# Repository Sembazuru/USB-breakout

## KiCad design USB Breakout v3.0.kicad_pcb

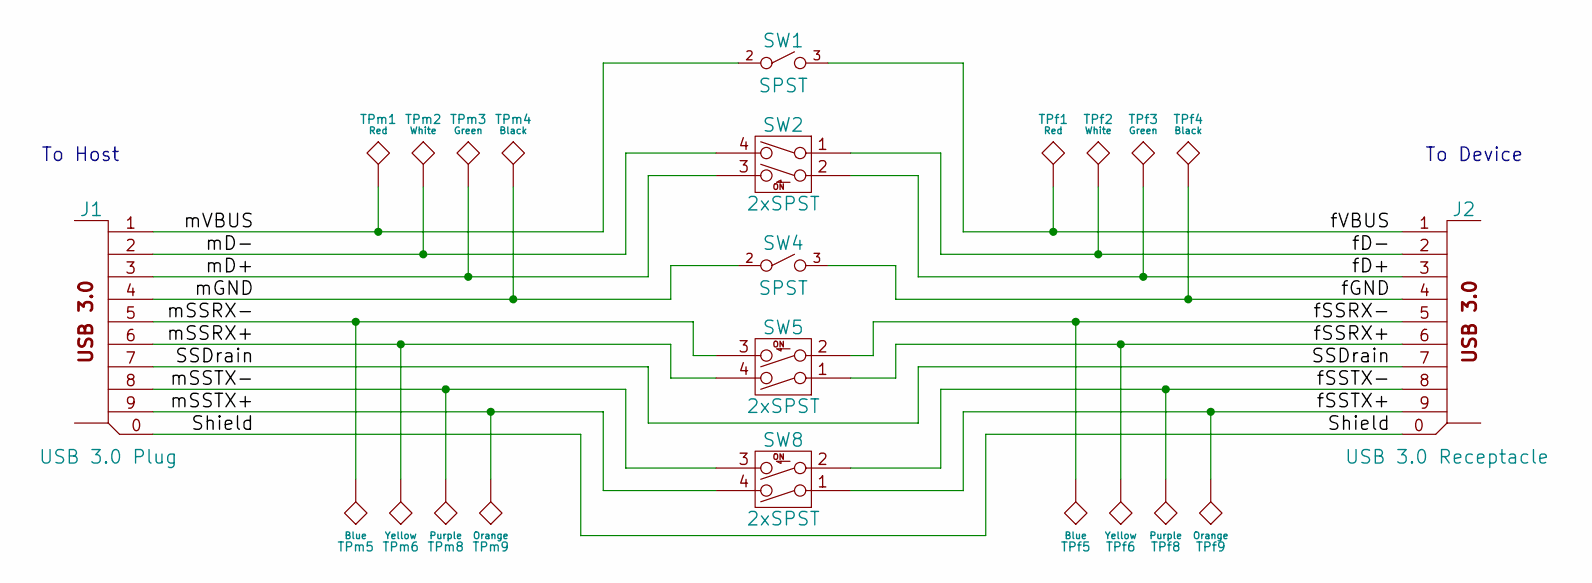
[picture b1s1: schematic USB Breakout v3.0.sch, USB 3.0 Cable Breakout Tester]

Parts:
J1: USB 3.0 Plug; Amphenol_GSB316441CEU
J2: USB 3.0 Receptacle; Amphenol_GSB311131HR
SW1, SW4: SPST; SW_Jameco2135478U
SW2, SW5, SW8: 2xSPST; DIPSW762W57P254L608H570Q4U
TPf1: Red; TESTPOINT
TPf2: White; TESTPOINT
TPf3: Green; TESTPOINT
TPf4: Black; TESTPOINT
TPf5: Blue; TESTPOINT
TPf6: Yellow; TESTPOINT
TPf8: Purple; TESTPOINT
TPf9: Orange; TESTPOINT
TPm1: Red; TESTPOINT
TPm2: White; TESTPOINT
TPm3: Green; TESTPOINT
TPm4: Black; TESTPOINT
TPm5: Blue; TESTPOINT
TPm6: Yellow; TESTPOINT
TPm8: Purple; TESTPOINT
TPm9: Orange; TESTPOINT

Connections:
/SSDrain: J1.7, J2.7
/Shield: J1.0, J2.0
/fD+: J2.3, SW2.2, TPf3.1
/fD-: J2.2, SW2.1, TPf2.1
/fGND: J2.4, SW4.3, TPf4.1
/fSSRX+: J2.6, SW5.1, TPf6.1
/fSSRX-: J2.5, SW5.2, TPf5.1
/fSSTX+: J2.9, SW8.1, TPf9.1
/fSSTX-: J2.8, SW8.2, TPf8.1
/fVBUS: J2.1, SW1.3, TPf1.1
/mD+: J1.3, SW2.3, TPm3.1
/mD-: J1.2, SW2.4, TPm2.1
/mGND: J1.4, SW4.2, TPm4.1
/mSSRX+: J1.6, SW5.4, TPm6.1
/mSSRX-: J1.5, SW5.3, TPm5.1
/mSSTX+: J1.9, SW8.4, TPm9.1
/mSSTX-: J1.8, SW8.3, TPm8.1
/mVBUS: J1.1, SW1.2, TPm1.1

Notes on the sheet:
To Host
To Device

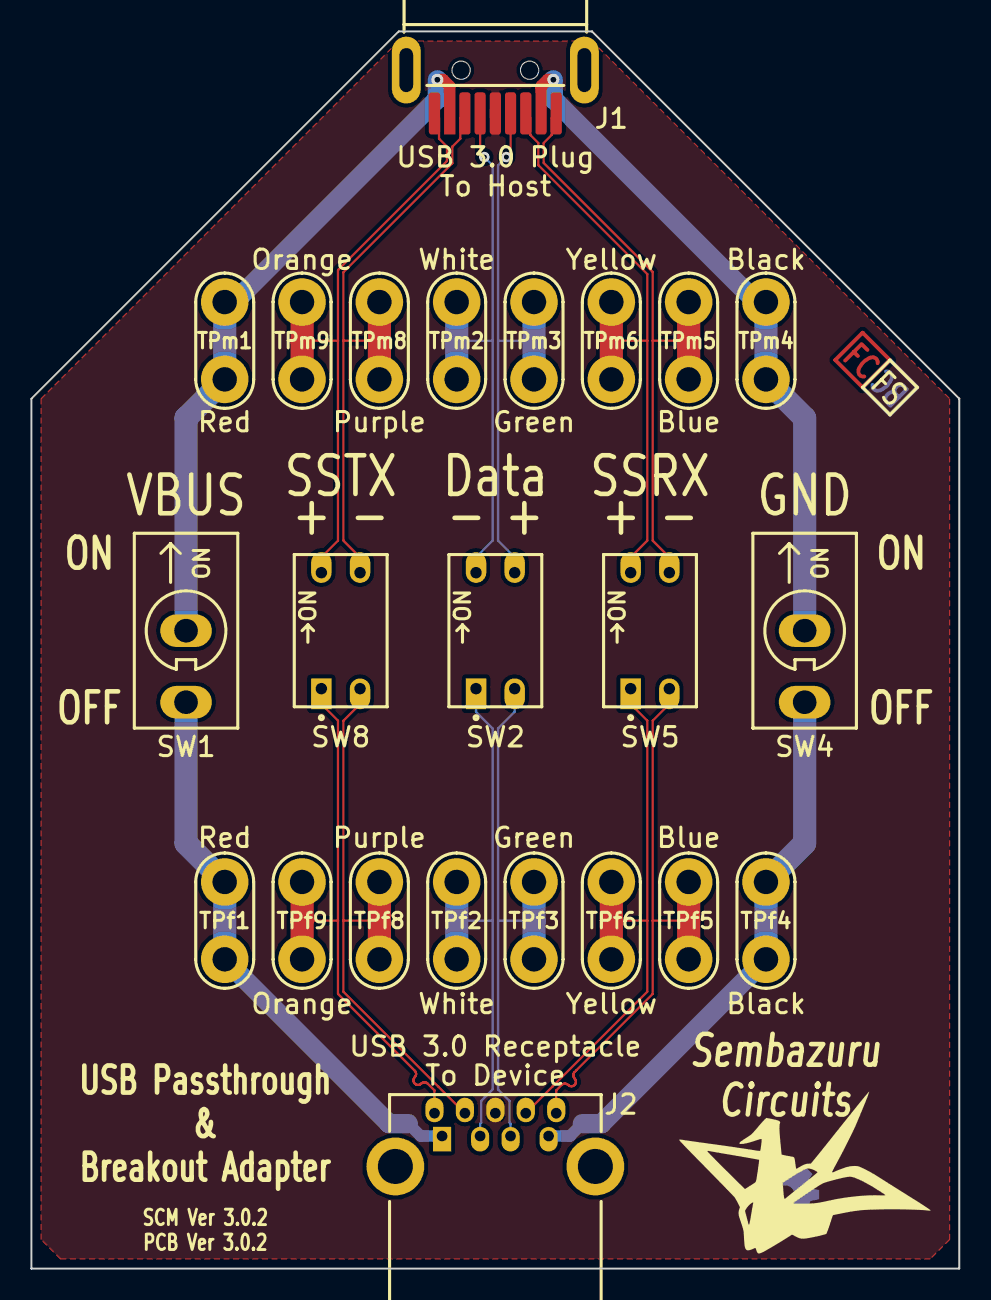
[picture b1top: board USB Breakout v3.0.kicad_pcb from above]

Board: 2 copper layers, 61.0 x 81.3 mm, 24 parts (0 on the bottom side), 18 nets.

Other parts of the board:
LayerIcon02: VAL**; LayerIcon02

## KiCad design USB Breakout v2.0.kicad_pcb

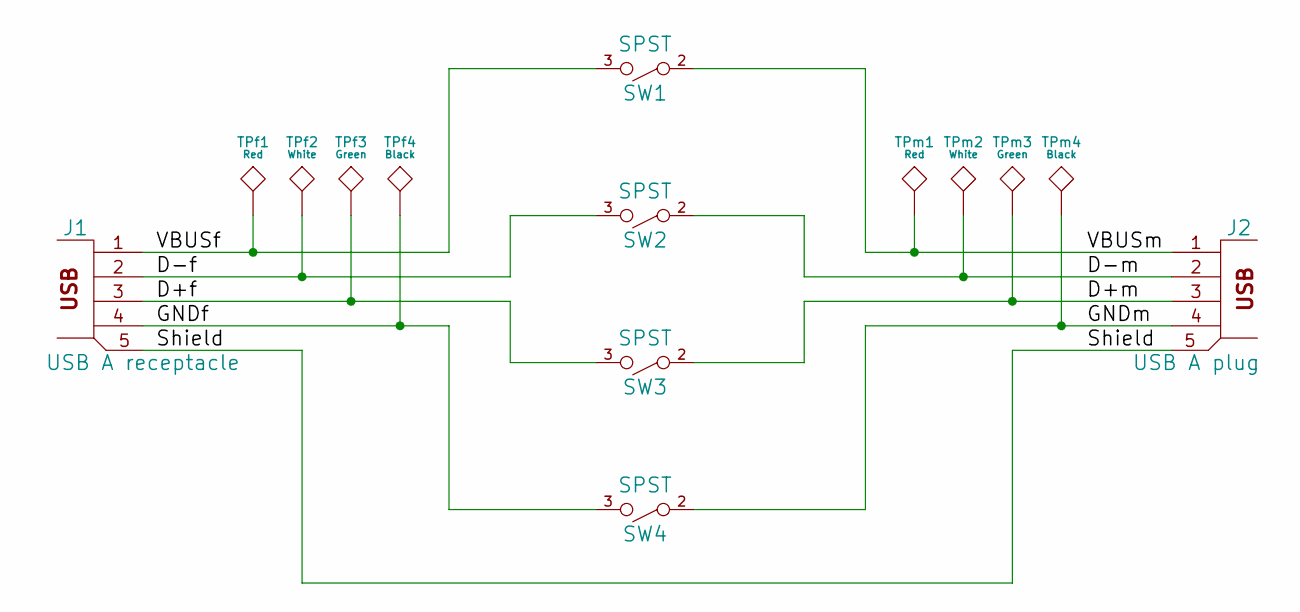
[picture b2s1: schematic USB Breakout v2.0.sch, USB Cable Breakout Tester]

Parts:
J1: USB A receptacle; TYCO_292303-1; MFG# 292303-1
J2: USB A plug; MOLEX_48037-0001; MFG# 48037-0001
SW1, SW2, SW3, SW4: SPST; SW_Jameco2135478; MFG# T100T1B4A2
TPf1: Red; TESTPOINT; MFG# 5010
TPf2: White; TESTPOINT; MFG# 5012
TPf3: Green; TESTPOINT; MFG# 5126
TPf4: Black; TESTPOINT; MFG# 5011
TPm1: Red; TESTPOINT; MFG# 5010
TPm2: White; TESTPOINT; MFG# 5012
TPm3: Green; TESTPOINT; MFG# 5126
TPm4: Black; TESTPOINT; MFG# 5011

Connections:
/D+f: J1.3, SW3.3, TPf3.1
/D+m: J2.3, SW3.2, TPm3.1
/D-f: J1.2, SW2.3, TPf2.1
/D-m: J2.2, SW2.2, TPm2.1
/GNDf: J1.4, SW4.3, TPf4.1
/GNDm: J2.4, SW4.2, TPm4.1
/Shield: J1.5, J2.5
/VBUSf: J1.1, SW1.3, TPf1.1
/VBUSm: J2.1, SW1.2, TPm1.1

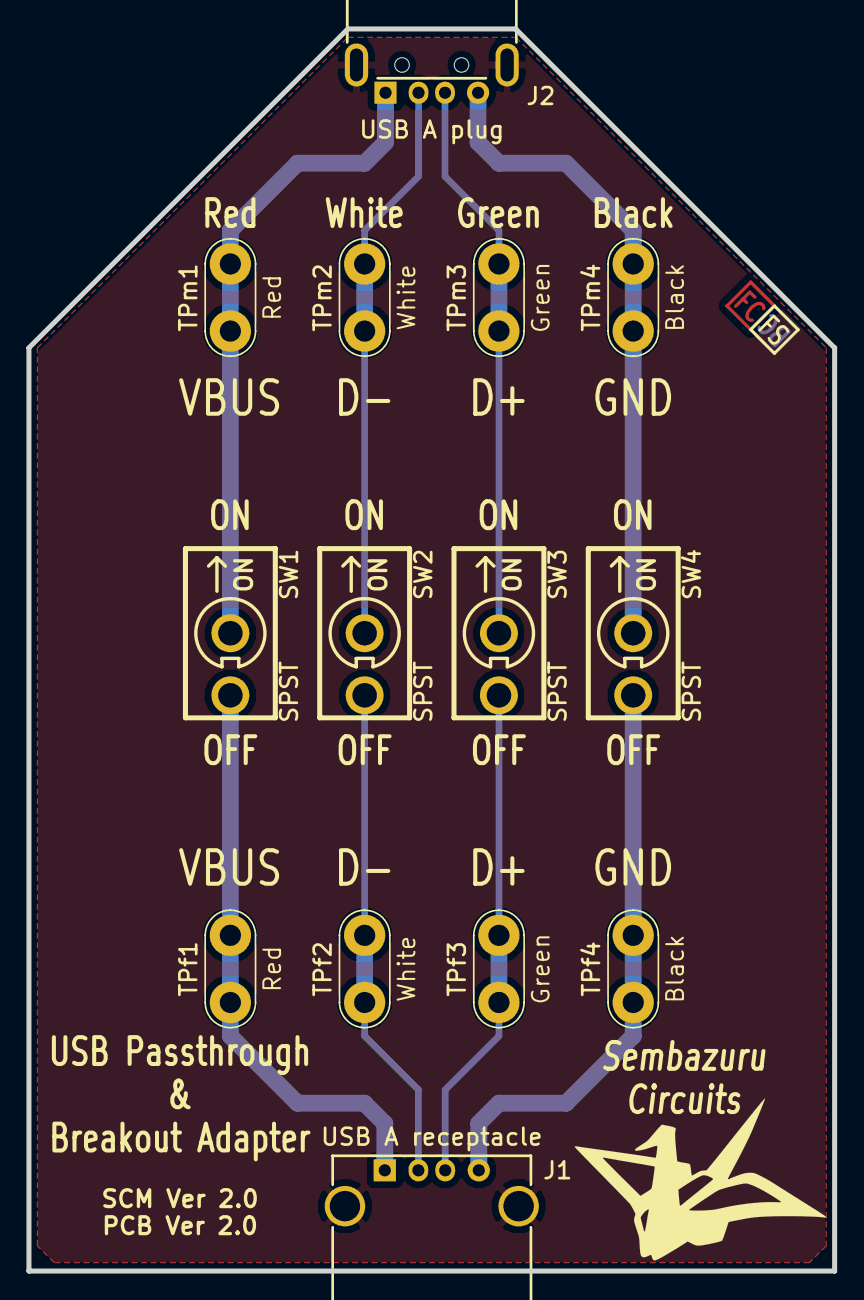
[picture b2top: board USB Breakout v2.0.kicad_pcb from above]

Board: 2 copper layers, 61.0 x 94.0 mm, 15 parts (0 on the bottom side), 9 nets.

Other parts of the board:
LayerIcon02: VAL**; LayerIcon02
